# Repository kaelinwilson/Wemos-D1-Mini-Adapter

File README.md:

# Wemos-D1-Mini-Adapter
An adapter board to suit the Wemos D1 Mini to the ESP8266 header

Update 04-10-2020: Changed board to suit ESP8266-MOD-WIFI connector

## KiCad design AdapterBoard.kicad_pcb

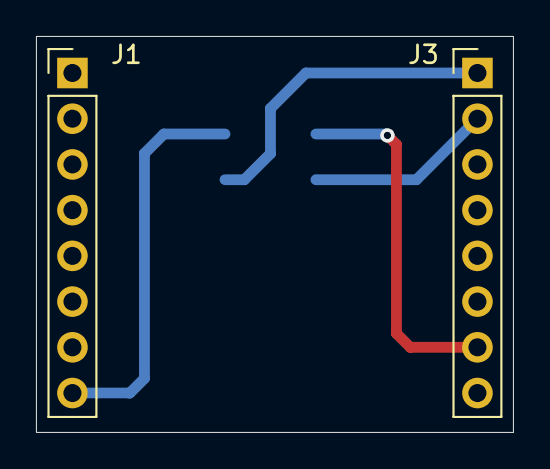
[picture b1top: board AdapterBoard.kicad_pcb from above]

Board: 2 copper layers, 26.5 x 22.0 mm, 3 parts (1 on the bottom side), 4 nets.

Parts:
J1: Conn_L; PinHeader_1x08_P2.54mm_Vertical
J2: Conn_Bot; PinHeader_2x05_P2.54mm_Vertical_SMD
J3: Conn_R; PinHeader_1x08_P2.54mm_Vertical

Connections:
unnamed: J1.8, J2.2
unnamed: J2.1, J3.7
unnamed: J2.3, J3.2
unnamed: J2.4, J3.1

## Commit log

2020-03-24 Rename AdapterBoard-B_Cu.gbr to gerbers/AdapterBoard-B_Cu.gbr
2020-03-24 Rename AdapterBoard-B_Mask.gbr to gerbers/AdapterBoard-B_Mask.gbr
2020-03-24 Rename AdapterBoard-B_Paste.gbr to gerbers/AdapterBoard-B_Paste.gbr
2020-03-24 Rename AdapterBoard-B_SilkS.gbr to gerbers/AdapterBoard-B_SilkS.gbr
2020-03-24 Rename AdapterBoard-Edge_Cuts.gbr to gerbers/AdapterBoard-Edge_Cuts.gbr
2020-03-24 Rename AdapterBoard-F_Cu.gbr to gerbers/AdapterBoard-F_Cu.gbr
2020-03-24 Rename AdapterBoard-F_Mask.gbr to gerbers/AdapterBoard-F_Mask.gbr
2020-03-24 Rename AdapterBoard-F_Paste.gbr to gerbers/AdapterBoard-F_Paste.gbr
2020-03-24 Rename AdapterBoard-F_SilkS.gbr to gerbers/AdapterBoard-F_SilkS.gbr
2020-03-24 Rename AdapterBoard-NPTH.drl to gerbers/AdapterBoard-NPTH.drl
2020-03-24 Rename AdapterBoard-PTH.drl to gerbers/AdapterBoard-PTH.drl
